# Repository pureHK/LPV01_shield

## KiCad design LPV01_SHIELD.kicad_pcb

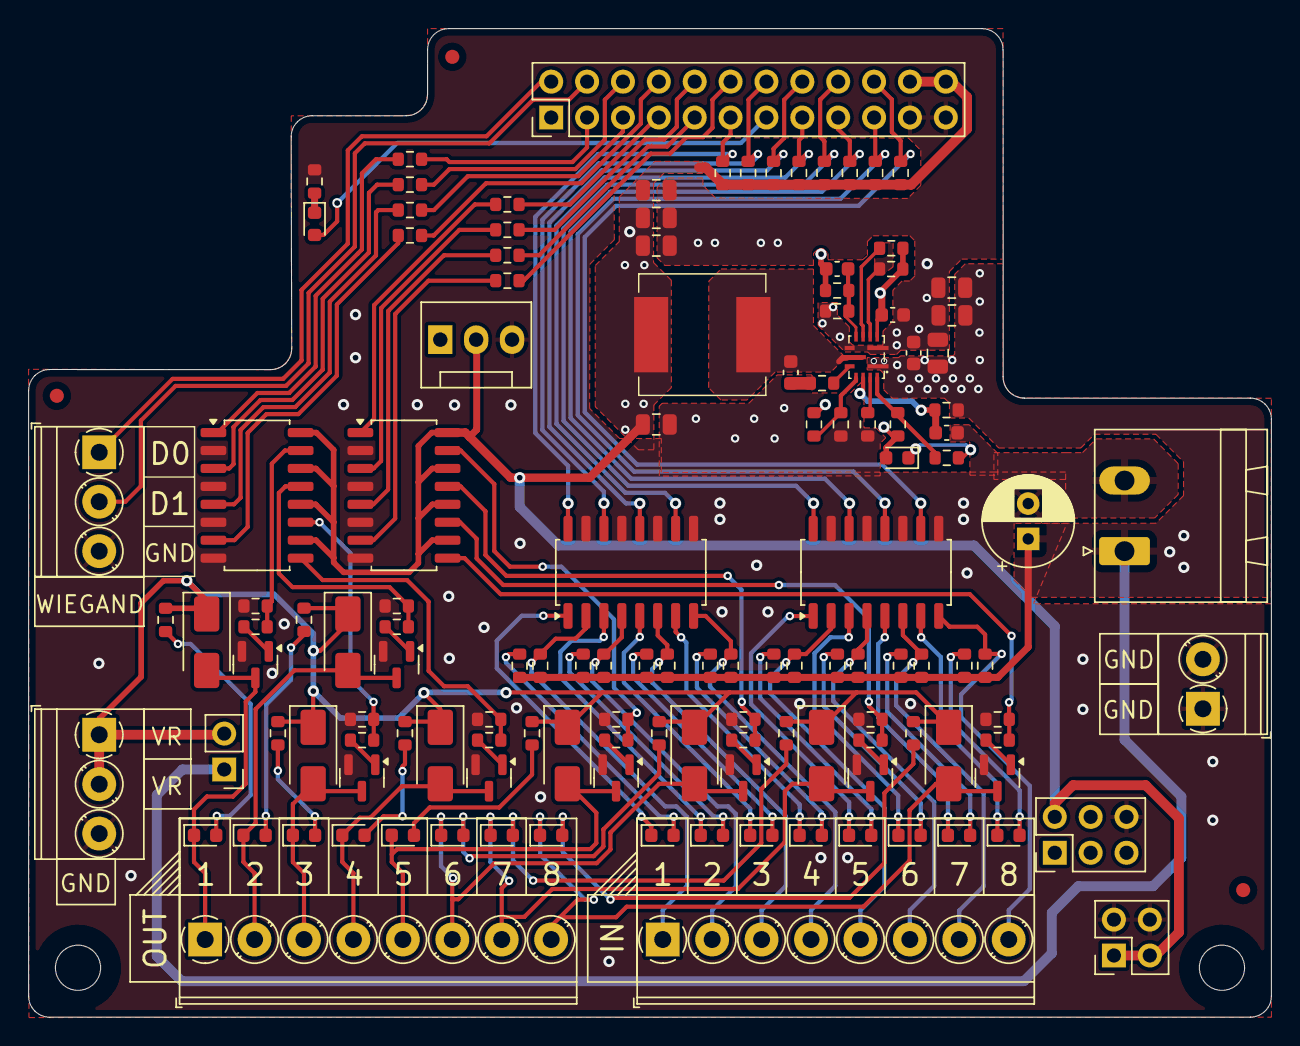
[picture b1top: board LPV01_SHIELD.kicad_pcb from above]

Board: 4 copper layers, 88.0 x 70.0 mm, 134 parts (0 on the bottom side), 100 nets.

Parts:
C1: 100u; CP_Radial_D6.3mm_P2.50mm
C2, C3, C4: 10u; C_0805_2012Metric
C5: 100n; C_0603_1608Metric
C6, C7, C8, C9: 22u; C_0805_2012Metric
C10: 1n; C_0603_1608Metric
C11: 2u2; C_0603_1608Metric
C12: 1u; C_0603_1608Metric
C13: 22p; C_0603_1608Metric
D1, D3, D5, D7, D9, D11, D13, D15, D18, D19, D20, D21, D22, D23, D24, D25, D26: LED; LED_0603_1608Metric
D2, D4, D6, D8, D10, D12, D14, D16: D; D_SMA
D17: STATUS; LED_0603_1608Metric
H1, H2: MountingHole; MountingHole_3.2mm_M3_DIN965
J1: GPIO_header; PinHeader_2x12_P2.54mm_Vertical
J2: PWR_socket; PinSocket_2x02_P2.54mm_Vertical
J3: SPI_header; PinHeader_2x03_P2.54mm_Vertical
J4, J6: Wiegand; TerminalBlock_Phoenix_PT-1,5-3-3.5-H_1x03_P3.50mm_Horizontal
J5: Conn_01x02_Pin; PinHeader_1x02_P2.54mm_Vertical
J7: Fan; FanPinHeader_1x03_P2.54mm_Vertical
J8, J9: Inputs; TerminalBlock_Phoenix_PT-1,5-8-3.5-H_1x08_P3.50mm_Horizontal
J10: Screw_Terminal_01x02; TerminalBlock_Phoenix_PT-1,5-2-3.5-H_1x02_P3.50mm_Horizontal
J11: PWR_input; PhoenixContact_MSTBA_2,5_2-G_1x02_P5.00mm_Horizontal
L1: 4u7; Inductor_IHLP3232DZER4R7M11_HK
Q1, Q2, Q3, Q4, Q5, Q6, Q7, Q8: BC817; SOT-23
R1, R2, R3, R4, R5, R6, R7, R8: 470R; R_0603_1608Metric
R9, R12, R15, R18, R21, R24, R27, R30: 22k; R_0603_1608Metric
R10, R13, R16, R19, R22, R25, R28, R31: 4k7; R_0603_1608Metric
R11, R14, R17, R20, R23, R26, R29, R32, R42, R43, R44, R45, R46, R47, R48, R49: 2k2; R_0603_1608Metric
R33, R62: 1k; R_0603_1608Metric
R34, R35, R36, R37, R38, R39, R40, R41, R50, R51, R52, R53, R54, R55, R56, R57, R59, R60, R64: 10k; R_0603_1608Metric
R58: 300k; R_0603_1608Metric
R61: 51k; R_0603_1608Metric
R63, R65, R66: 0; R_0603_1608Metric
R67: 100k; R_0603_1608Metric
R68: 11k; R_0603_1608Metric
U1: MP2491C; QFN-13_HK
U2, U3, U4, U5: TCMT4100; SOP-16_4.4x10.4mm_P1.27mm

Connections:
+5V: C6.1, C7.1, C8.1, C9.1, C13.1, J1.22, J1.24, J2.1, J2.2, J3.2, J7.2, L1.2, R50.1, R51.1, R52.1, R53.1, R54.1, R55.1, R56.1, R57.1, R67.1, U2.10, U2.12, U2.14, U2.16, U3.10, U3.12, U3.14, U3.16
+24V: C1.1, C2.1, C3.1, C4.1, C5.1, J5.1, J11.1, R34.1, R35.1, R36.1, R37.1, R38.1, R39.1, R40.1, R41.1, R42.2, R43.2, R44.2, R45.2, R46.2, R47.2, R48.2, R49.2, R58.1, U1.1 (IN)
/O1: R9.1, R10.1, U2.15
/O2: R12.1, R13.1, U2.13
/O3: R15.1, R16.1, U2.11
/O4: R18.1, R19.1, U2.9
/O5: R21.1, R22.1, U3.15
/O6: R24.1, R25.1, U3.13
/O7: R27.1, R28.1, U3.11
/O8: R30.1, R31.1, U3.9
/OUT1: D1.1 (K), D2.2 (A), J8.1, Q1.3 (C)
/OUT2: D3.1 (K), D4.2 (A), J8.2, Q2.3 (C)
/OUT3: D5.1 (K), D6.2 (A), J8.3, Q3.3 (C)
/OUT4: D7.1 (K), D8.2 (A), J8.4, Q4.3 (C)
/OUT5: D9.1 (K), D10.2 (A), J8.5, Q5.3 (C)
/OUT6: D11.1 (K), D12.2 (A), J8.6, Q6.3 (C)
/OUT7: D13.1 (K), D14.2 (A), J8.7, Q7.3 (C)
/OUT8: D15.1 (K), D16.2 (A), J8.8, Q8.3 (C)
D0: J1.2, J6.1
D1: J1.4, J6.2
D2: J1.6, R2.2
D3: J1.8, R4.2
D4: J1.10, R6.2
D5: J1.12, R8.2
D6: J1.14, R51.2, U4.14
D8: J1.3, R1.2
D9: J1.5, R3.2
D10: J1.7, R5.2
D11: J1.9, R7.2
D12: J1.11, R50.2, U4.16
D13: D17.2 (A), J1.13
D18: J1.16, R52.2, U4.12
D19: J1.18, R54.2, U5.16
D20: J1.20, R57.2, U5.10
D21: J1.15, R53.2, U4.10
D22: J1.17, R55.2, U5.14
D23: J1.19, R56.2, U5.12
GND: C1.2, C2.2, C3.2, C4.2, C5.2, C6.2, C7.2, C8.2, C9.2, C10.2, C11.2, J1.21, J1.23, J2.3, J2.4, J3.6, J4.3, J6.3, J7.3, J10.1, J10.2, J11.2, Q1.2 (E), Q2.2 (E), Q3.2 (E), Q4.2 (E), Q5.2 (E), Q6.2 (E), Q7.2 (E), Q8.2 (E), R9.2, R12.2, R15.2, R18.2, R21.2, R24.2, R27.2, R30.2, R33.1, R61.2, R66.2, R68.2, U1.2 (PGND), U1.7 (AGND), U2.2, U2.4, U2.6, U2.8, U3.2, U3.4, U3.6, U3.8, U4.9, U4.11, U4.13, U4.15, U5.9, U5.11, U5.13, U5.15
unnamed: C12.2, R63.2
unnamed: D1.2 (A), R11.2
unnamed: D3.2 (A), R14.2
unnamed: D5.2 (A), R17.2
unnamed: D7.2 (A), R20.2
unnamed: D9.2 (A), R23.2
unnamed: D11.2 (A), R26.2
unnamed: D13.2 (A), R29.2
unnamed: D15.2 (A), R32.2
unnamed: D17.1 (K), R33.2
unnamed: D18.2 (A), R42.1
unnamed: D18.1 (K), U4.1
unnamed: D19.2 (A), R43.1
unnamed: D19.1 (K), U4.3
unnamed: D20.2 (A), R44.1
unnamed: D20.1 (K), U4.5
unnamed: D21.2 (A), R45.1
unnamed: D21.1 (K), U4.7
unnamed: D22.2 (A), R46.1
unnamed: D22.1 (K), U5.1
unnamed: D23.2 (A), R47.1
unnamed: D23.1 (K), U5.3
unnamed: D24.2 (A), R48.1
unnamed: D24.1 (K), U5.5
unnamed: D25.2 (A), R49.1
unnamed: D25.1 (K), U5.7
unnamed: D26.1 (K), R62.1
unnamed: J9.1, R34.2, U4.2
unnamed: J9.2, R35.2, U4.4
unnamed: J9.3, R36.2, U4.6
unnamed: J9.4, R37.2, U4.8
unnamed: J9.5, R38.2, U5.2
unnamed: J9.6, R39.2, U5.4
unnamed: J9.7, R40.2, U5.6
unnamed: J9.8, R41.2, U5.8
unnamed: Q1.1 (B), R10.2
unnamed: Q2.1 (B), R13.2
unnamed: Q3.1 (B), R16.2
unnamed: Q4.1 (B), R19.2
unnamed: Q5.1 (B), R22.2
unnamed: Q6.1 (B), R25.2
unnamed: Q7.1 (B), R28.2
unnamed: Q8.1 (B), R31.2
unnamed: R1.1, U2.1
unnamed: R2.1, U2.3
unnamed: R3.1, U2.5
unnamed: R4.1, U2.7
unnamed: R5.1, U3.1
unnamed: R6.1, U3.3
unnamed: R7.1, U3.5
unnamed: R8.1, U3.7
unnamed: R63.1, U1.9 (BST)
unnamed: C10.1, R58.2, U1.11 (EN)
unnamed: C13.2, R67.2, R68.1, U1.6 (FB)
unnamed: R61.1, U1.12 (ILIM)
unnamed: R65.1, R66.1, U1.10 (MODE)
unnamed: R62.2, R64.1, U1.13 (PG)
unnamed: C12.1, L1.1, U1.8 (SW)
unnamed: R59.2, U1.4 (VSEL1)
unnamed: R60.2, U1.5 (VSEL2)
VCC: C11.1, D26.2 (A), R59.1, R60.1, R64.2, R65.2, U1.3 (VCC)
VR: D2.1 (K), D4.1 (K), D6.1 (K), D8.1 (K), D10.1 (K), D12.1 (K), D14.1 (K), D16.1 (K), J4.1, J4.2, J5.2, R11.1, R14.1, R17.1, R20.1, R23.1, R26.1, R29.1, R32.1

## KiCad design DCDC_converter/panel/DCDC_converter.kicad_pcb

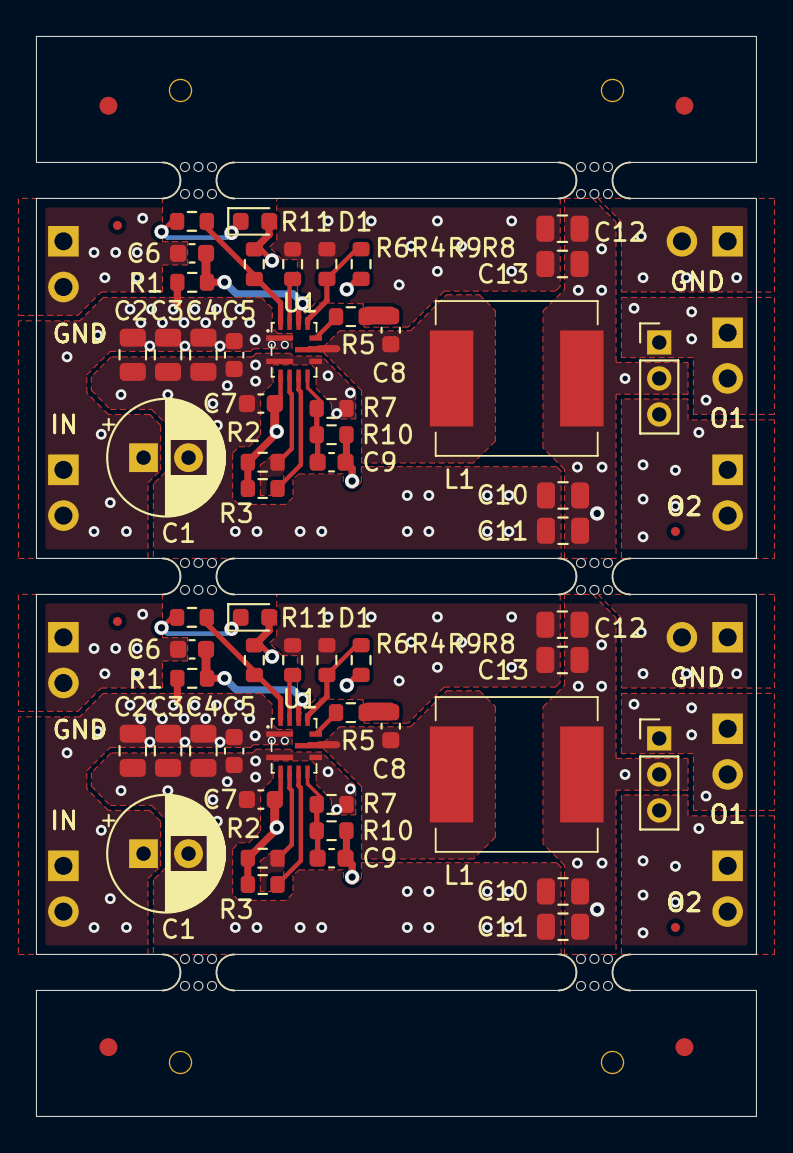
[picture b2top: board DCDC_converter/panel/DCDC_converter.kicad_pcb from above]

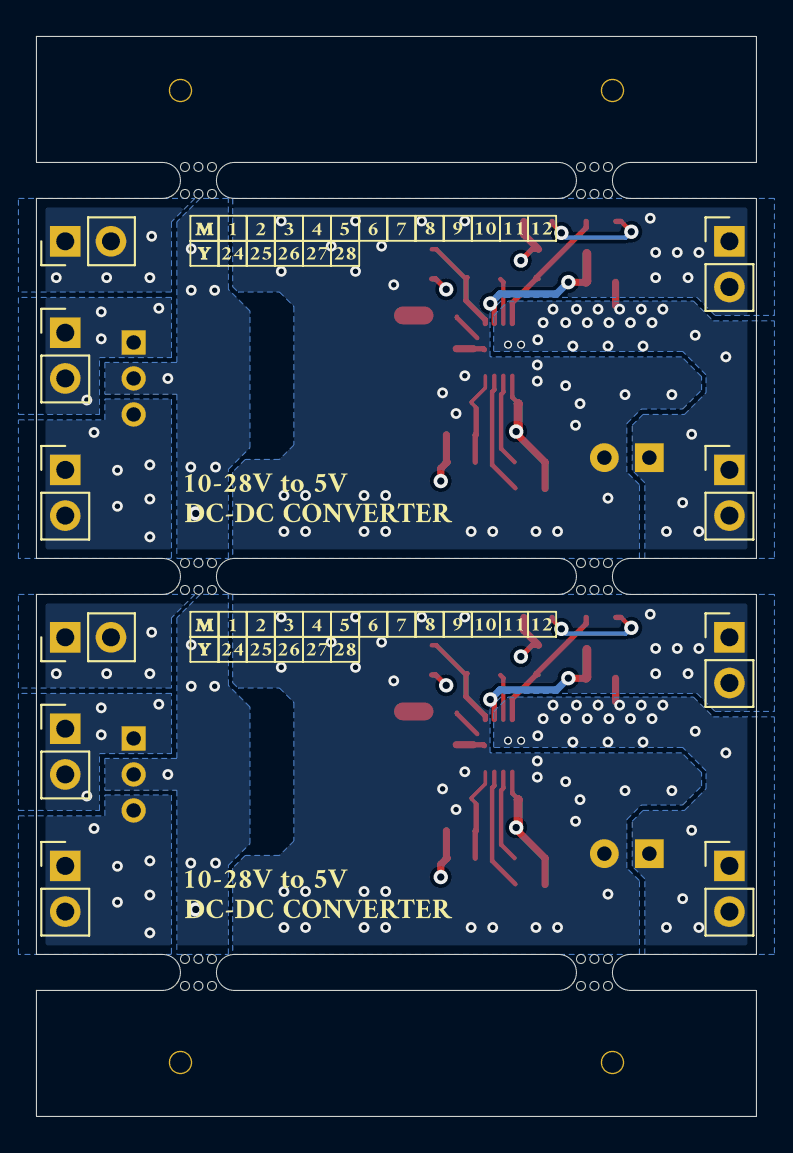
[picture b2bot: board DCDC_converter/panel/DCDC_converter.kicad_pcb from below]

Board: 4 copper layers, 40.0 x 60.0 mm, 72 parts (10 on the bottom side), 17 nets.

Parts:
C1, C14: 100u; CP_Radial_D6.3mm_P2.50mm
C2, C3, C4, C15, C16, C17: 10u; C_0805_2012Metric
C5, C18: 100n; C_0603_1608Metric
C6, C19: 1n; C_0603_1608Metric
C7, C20: 2u2; C_0603_1608Metric
C8, C21: 1u; C_0603_1608Metric
C9, C22: 22p; C_0603_1608Metric
C10, C11, C12, C13, C23, C24, C25, C26: 22u; C_0805_2012Metric
D1, D2: LED; LED_0603_1608Metric
J1, J2, J3, J4, J6, J7, J8, J9, J10, J12: Conn_01x02_Pin; PinHeader_1x02_P2.54mm_Vertical
J5, J11: Conn_01x03_Pin; PinHeader_1x03_P2.00mm_Vertical
L1, L2: 4u7; Inductor_IHLP3232DZER4R7M11_HK
R1, R12: 300k; R_0603_1608Metric
R2, R3, R6, R13, R14, R17: 10k; R_0603_1608Metric
R4, R15: 51k; R_0603_1608Metric
R5, R8, R9, R16, R19, R20: 0; R_0603_1608Metric
R7, R18: 11k; R_0603_1608Metric
R10, R21: 100k; R_0603_1608Metric
R11, R22: 1k; R_0603_1608Metric
U1, U2: MP2491C; QFN-13_HK
mouse-bite-2mm-slot, mouse-bite-2mm-slot#2, mouse-bite-2mm-slot#3, mouse-bite-2mm-slot#4, mouse-bite-2mm-slot#5, mouse-bite-2mm-slot#6: VAL**; mouse-bite-2mm-slot

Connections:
+5V: C9.1, C10.1, C11.1, C12.1, C13.1, C22.1, C23.1, C24.1, C25.1, C26.1, J5.2, J11.2, L1.2, L2.2, R10.1, R21.1
+24V: C1.1, C2.1, C3.1, C4.1, C5.1, C14.1, C15.1, C16.1, C17.1, C18.1, J1.1, J1.2, J7.1, J7.2, R1.1, R12.1, U1.1 (IN), U2.1 (IN)
GND: C1.2, C2.2, C3.2, C4.2, C5.2, C6.2, C7.2, C10.2, C11.2, C12.2, C13.2, C14.2, C15.2, C16.2, C17.2, C18.2, C19.2, C20.2, C23.2, C24.2, C25.2, C26.2, J2.1, J2.2, J4.1, J4.2, J8.1, J8.2, J10.1, J10.2, R4.2, R7.2, R9.2, R15.2, R18.2, R20.2, U1.2 (PGND), U1.7 (AGND), U2.2 (PGND), U2.7 (AGND)
unnamed: C8.2, C21.2, R5.2, R16.2
unnamed: D1.1 (K), D2.1 (K), R11.1, R22.1
unnamed: J3.1, J3.2, J5.1, J9.1, J9.2, J11.1
unnamed: J5.3, J6.1, J6.2, J11.3, J12.1, J12.2
unnamed: R5.1, R16.1, U1.9 (BST), U2.9 (BST)
unnamed: C6.1, C19.1, R1.2, R12.2, U1.11 (EN), U2.11 (EN)
unnamed: C9.2, C22.2, R7.1, R10.2, R18.1, R21.2, U1.6 (FB), U2.6 (FB)
unnamed: R4.1, R15.1, U1.12 (ILIM), U2.12 (ILIM)
unnamed: R8.1, R9.1, R19.1, R20.1, U1.10 (MODE), U2.10 (MODE)
unnamed: R6.1, R11.2, R17.1, R22.2, U1.13 (PG), U2.13 (PG)
unnamed: C8.1, C21.1, L1.1, L2.1, U1.8 (SW), U2.8 (SW)
unnamed: R2.2, R13.2, U1.4 (VSEL1), U2.4 (VSEL1)
unnamed: R3.2, R14.2, U1.5 (VSEL2), U2.5 (VSEL2)
VCC: C7.1, C20.1, D1.2 (A), D2.2 (A), R2.1, R3.1, R6.2, R8.2, R13.1, R14.1, R17.2, R19.2, U1.3 (VCC), U2.3 (VCC)

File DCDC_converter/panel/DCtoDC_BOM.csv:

Reference,Value,Footprint,LCSC part number
C1,"100u,50V",Capacitor_THT:CP_Radial_D6.3mm_P2.50mm, C160200
C2,"10u,50V",Capacitor_SMD:C_0805_2012Metric,
C3,"10u,50V",Capacitor_SMD:C_0805_2012Metric,
C4,"10u,50V",Capacitor_SMD:C_0805_2012Metric,
C5,100n,Capacitor_SMD:C_0603_1608Metric,
C6,1n,Capacitor_SMD:C_0603_1608Metric,
C7,2u2,Capacitor_SMD:C_0603_1608Metric,
C8,1u,Capacitor_SMD:C_0603_1608Metric,
C9,22p,Capacitor_SMD:C_0603_1608Metric,
C10,22u,Capacitor_SMD:C_0805_2012Metric,
C11,22u,Capacitor_SMD:C_0805_2012Metric,
C12,22u,Capacitor_SMD:C_0805_2012Metric,
C13,22u,Capacitor_SMD:C_0805_2012Metric,
D1,LED,LED_SMD:LED_0603_1608Metric,
L1,4u7,HK:Inductor_IHLP3232DZER4R7M11_HK, C845059
R1,300k,Resistor_SMD:R_0603_1608Metric,
R2,10k,Resistor_SMD:R_0603_1608Metric,
R3,10k,Resistor_SMD:R_0603_1608Metric,
R4,51k,Resistor_SMD:R_0603_1608Metric,
R5,0,Resistor_SMD:R_0603_1608Metric,
R6,10k,Resistor_SMD:R_0603_1608Metric,
R7,11k,Resistor_SMD:R_0603_1608Metric,
R8,0,Resistor_SMD:R_0603_1608Metric,
R9,0,Resistor_SMD:R_0603_1608Metric,
R10,100k,Resistor_SMD:R_0603_1608Metric,
R11,1k,Resistor_SMD:R_0603_1608Metric,
U1,MP2491C,QFN-13, C3187970
C14,"100u,50V",Capacitor_THT:CP_Radial_D6.3mm_P2.50mm, C160200
C15,"10u,50V",Capacitor_SMD:C_0805_2012Metric,
C16,"10u,50V",Capacitor_SMD:C_0805_2012Metric,
C17,"10u,50V",Capacitor_SMD:C_0805_2012Metric,
C18,100n,Capacitor_SMD:C_0603_1608Metric,
C19,1n,Capacitor_SMD:C_0603_1608Metric,
C20,2u2,Capacitor_SMD:C_0603_1608Metric,
C21,1u,Capacitor_SMD:C_0603_1608Metric,
C22,22p,Capacitor_SMD:C_0603_1608Metric,
C23,22u,Capacitor_SMD:C_0805_2012Metric,
C24,22u,Capacitor_SMD:C_0805_2012Metric,
C25,22u,Capacitor_SMD:C_0805_2012Metric,
C26,22u,Capacitor_SMD:C_0805_2012Metric,
D2,LED,LED_SMD:LED_0603_1608Metric,
L2,4u7,HK:Inductor_IHLP3232DZER4R7M11_HK, C845059
R12,300k,Resistor_SMD:R_0603_1608Metric,
R13,10k,Resistor_SMD:R_0603_1608Metric,
R14,10k,Resistor_SMD:R_0603_1608Metric,
R15,51k,Resistor_SMD:R_0603_1608Metric,
R16,0,Resistor_SMD:R_0603_1608Metric,
R17,10k,Resistor_SMD:R_0603_1608Metric,
R18,11k,Resistor_SMD:R_0603_1608Metric,
R19,0,Resistor_SMD:R_0603_1608Metric,
R20,0,Resistor_SMD:R_0603_1608Metric,
R21,100k,Resistor_SMD:R_0603_1608Metric,
R22,1k,Resistor_SMD:R_0603_1608Metric,
U2,MP2491C,QFN-13, C3187970

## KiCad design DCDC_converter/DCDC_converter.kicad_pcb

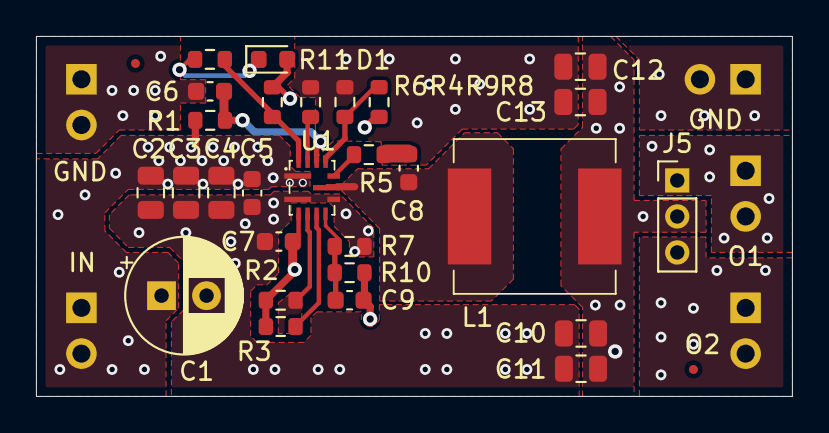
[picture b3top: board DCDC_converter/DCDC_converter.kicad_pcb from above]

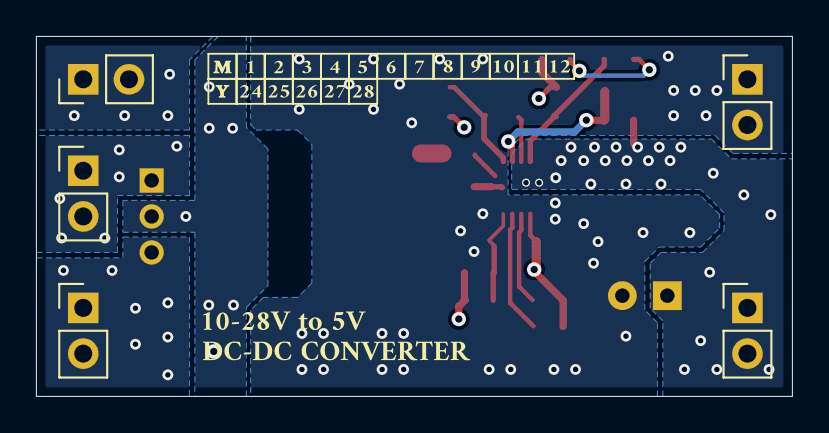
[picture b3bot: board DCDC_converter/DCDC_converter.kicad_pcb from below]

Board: 4 copper layers, 42.0 x 20.0 mm, 33 parts (5 on the bottom side), 17 nets.

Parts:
C1: 100u; CP_Radial_D6.3mm_P2.50mm
C2, C3, C4: 10u; C_0805_2012Metric
C5: 100n; C_0603_1608Metric
C6: 1n; C_0603_1608Metric
C7: 2u2; C_0603_1608Metric
C8: 1u; C_0603_1608Metric
C9: 22p; C_0603_1608Metric
C10, C11, C12, C13: 22u; C_0805_2012Metric
D1: LED; LED_0603_1608Metric
J1, J2, J3, J4, J6: Conn_01x02_Pin; PinHeader_1x02_P2.54mm_Vertical
J5: Conn_01x03_Pin; PinHeader_1x03_P2.00mm_Vertical
L1: 4u7; Inductor_IHLP3232DZER4R7M11_HK
R1: 300k; R_0603_1608Metric
R2, R3, R6: 10k; R_0603_1608Metric
R4: 51k; R_0603_1608Metric
R5, R8, R9: 0; R_0603_1608Metric
R7: 11k; R_0603_1608Metric
R10: 100k; R_0603_1608Metric
R11: 1k; R_0603_1608Metric
U1: MP2491C; QFN-13_HK

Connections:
+5V: C9.1, C10.1, C11.1, C12.1, C13.1, J5.2, L1.2, R10.1
+24V: C1.1, C2.1, C3.1, C4.1, C5.1, J1.1, J1.2, R1.1, U1.1 (IN)
GND: C1.2, C2.2, C3.2, C4.2, C5.2, C6.2, C7.2, C10.2, C11.2, C12.2, C13.2, J2.1, J2.2, J4.1, J4.2, R4.2, R7.2, R9.2, U1.2 (PGND), U1.7 (AGND)
unnamed: C8.2, R5.2
unnamed: D1.1 (K), R11.1
unnamed: J3.1, J3.2, J5.1
unnamed: J5.3, J6.1, J6.2
unnamed: R5.1, U1.9 (BST)
unnamed: C6.1, R1.2, U1.11 (EN)
unnamed: C9.2, R7.1, R10.2, U1.6 (FB)
unnamed: R4.1, U1.12 (ILIM)
unnamed: R8.1, R9.1, U1.10 (MODE)
unnamed: R6.1, R11.2, U1.13 (PG)
unnamed: C8.1, L1.1, U1.8 (SW)
unnamed: R2.2, U1.4 (VSEL1)
unnamed: R3.2, U1.5 (VSEL2)
VCC: C7.1, D1.2 (A), R2.1, R3.1, R6.2, R8.2, U1.3 (VCC)

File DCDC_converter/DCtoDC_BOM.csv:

Reference,Value,Footprint,LCSC part number
C1,"100u,50V",Capacitor_THT:CP_Radial_D6.3mm_P2.50mm, C160200
C2,"10u,50V",Capacitor_SMD:C_0805_2012Metric,
C3,"10u,50V",Capacitor_SMD:C_0805_2012Metric,
C4,"10u,50V",Capacitor_SMD:C_0805_2012Metric,
C5,100n,Capacitor_SMD:C_0603_1608Metric,
C6,1n,Capacitor_SMD:C_0603_1608Metric,
C7,2u2,Capacitor_SMD:C_0603_1608Metric,
C8,1u,Capacitor_SMD:C_0603_1608Metric,
C9,22p,Capacitor_SMD:C_0603_1608Metric,
C10,22u,Capacitor_SMD:C_0805_2012Metric,
C11,22u,Capacitor_SMD:C_0805_2012Metric,
C12,22u,Capacitor_SMD:C_0805_2012Metric,
C13,22u,Capacitor_SMD:C_0805_2012Metric,
D1,LED,LED_SMD:LED_0603_1608Metric,
J1,Conn_01x02_Pin,Connector_PinHeader_2.54mm:PinHeader_1x02_P2.54mm_Vertical,
J2,Conn_01x02_Pin,Connector_PinHeader_2.54mm:PinHeader_1x02_P2.54mm_Vertical,
J3,Conn_01x02_Pin,Connector_PinHeader_2.54mm:PinHeader_1x02_P2.54mm_Vertical,
J4,Conn_01x02_Pin,Connector_PinHeader_2.54mm:PinHeader_1x02_P2.54mm_Vertical,
J5,Conn_01x03_Pin,Connector_PinHeader_2.54mm:PinHeader_1x03_P2.54mm_Vertical,
J6,Conn_01x02_Pin,Connector_PinHeader_2.54mm:PinHeader_1x02_P2.54mm_Vertical,
L1,4u7,HK:Inductor_IHLP3232DZER4R7M11_HK, C845059
R1,300k,Resistor_SMD:R_0603_1608Metric,
R2,10k,Resistor_SMD:R_0603_1608Metric,
R3,10k,Resistor_SMD:R_0603_1608Metric,
R4,51k,Resistor_SMD:R_0603_1608Metric,
R5,0,Resistor_SMD:R_0603_1608Metric,
R6,10k,Resistor_SMD:R_0603_1608Metric,
R7,11k,Resistor_SMD:R_0603_1608Metric,
R8,0,Resistor_SMD:R_0603_1608Metric,
R9,0,Resistor_SMD:R_0603_1608Metric,
R10,100k,Resistor_SMD:R_0603_1608Metric,
R11,1k,Resistor_SMD:R_0603_1608Metric,
U1,MP2491C,QFN-13, C3187970

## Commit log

2024-10-06 Added some terminals and assigned footprints
2024-10-06 Lengthening the board
2024-10-06 Length change
2024-10-06 Straightening one edge of PCB
2024-10-06 Added power schematic
2024-10-07 Power schematic update of one DC/DC converter
2024-10-07 Added values for passive elements near DC/DC
2024-10-10 Made custom solo PCB for DC/DC converter
2024-10-10 Adjusting elements placement
2024-10-10 Changing number of layers of PCB
2024-10-10 Last update
2024-10-12 Adjusting the size of the PCB
2024-10-12 Power PCB done
2024-10-12 Changed width of SW trace
2024-10-12 Gerbers and drill files generated
2024-10-12 Cleaning up the DC/DC project
2024-10-12 Fabricatoin files generated
2024-10-13 Made all the holes to be >= 0.3mm
2024-10-13 Preparing for panelizing
2024-10-13 Panelizing
2024-10-13 Panel repaired
2024-10-16 DCtoDC alterations to the panel
2024-10-17 Changes in schematic to fit DC/DC converter
2024-10-17 Final version of DC/DC module
2024-10-17 Flipping the headers to bottom side
2024-10-21 Bigger gaps between +24V and GND
2024-10-21 Added a panel of DCtoDC
2024-10-23 Added 2 schematic sheets
2024-10-26 Added inputs and outputs to the schematic
2024-10-27 PCB rebuilt
2024-10-27 First traces added
2024-10-27 Adjusting nets
2024-10-27 More traces + components alignment
2024-10-27 Adjustments to the traces
2024-10-28 Changed length of the PCB
2024-10-30 Made the PCK the size of the LP board
2024-11-02 PCB shortened to final measurements
2024-11-02 Making fields of copper
2024-11-02 Small adjustments to traces near OUT
2024-11-03 Added fan connector
2024-11-03 Filled all the fields
2024-11-03 Version 1 finished
